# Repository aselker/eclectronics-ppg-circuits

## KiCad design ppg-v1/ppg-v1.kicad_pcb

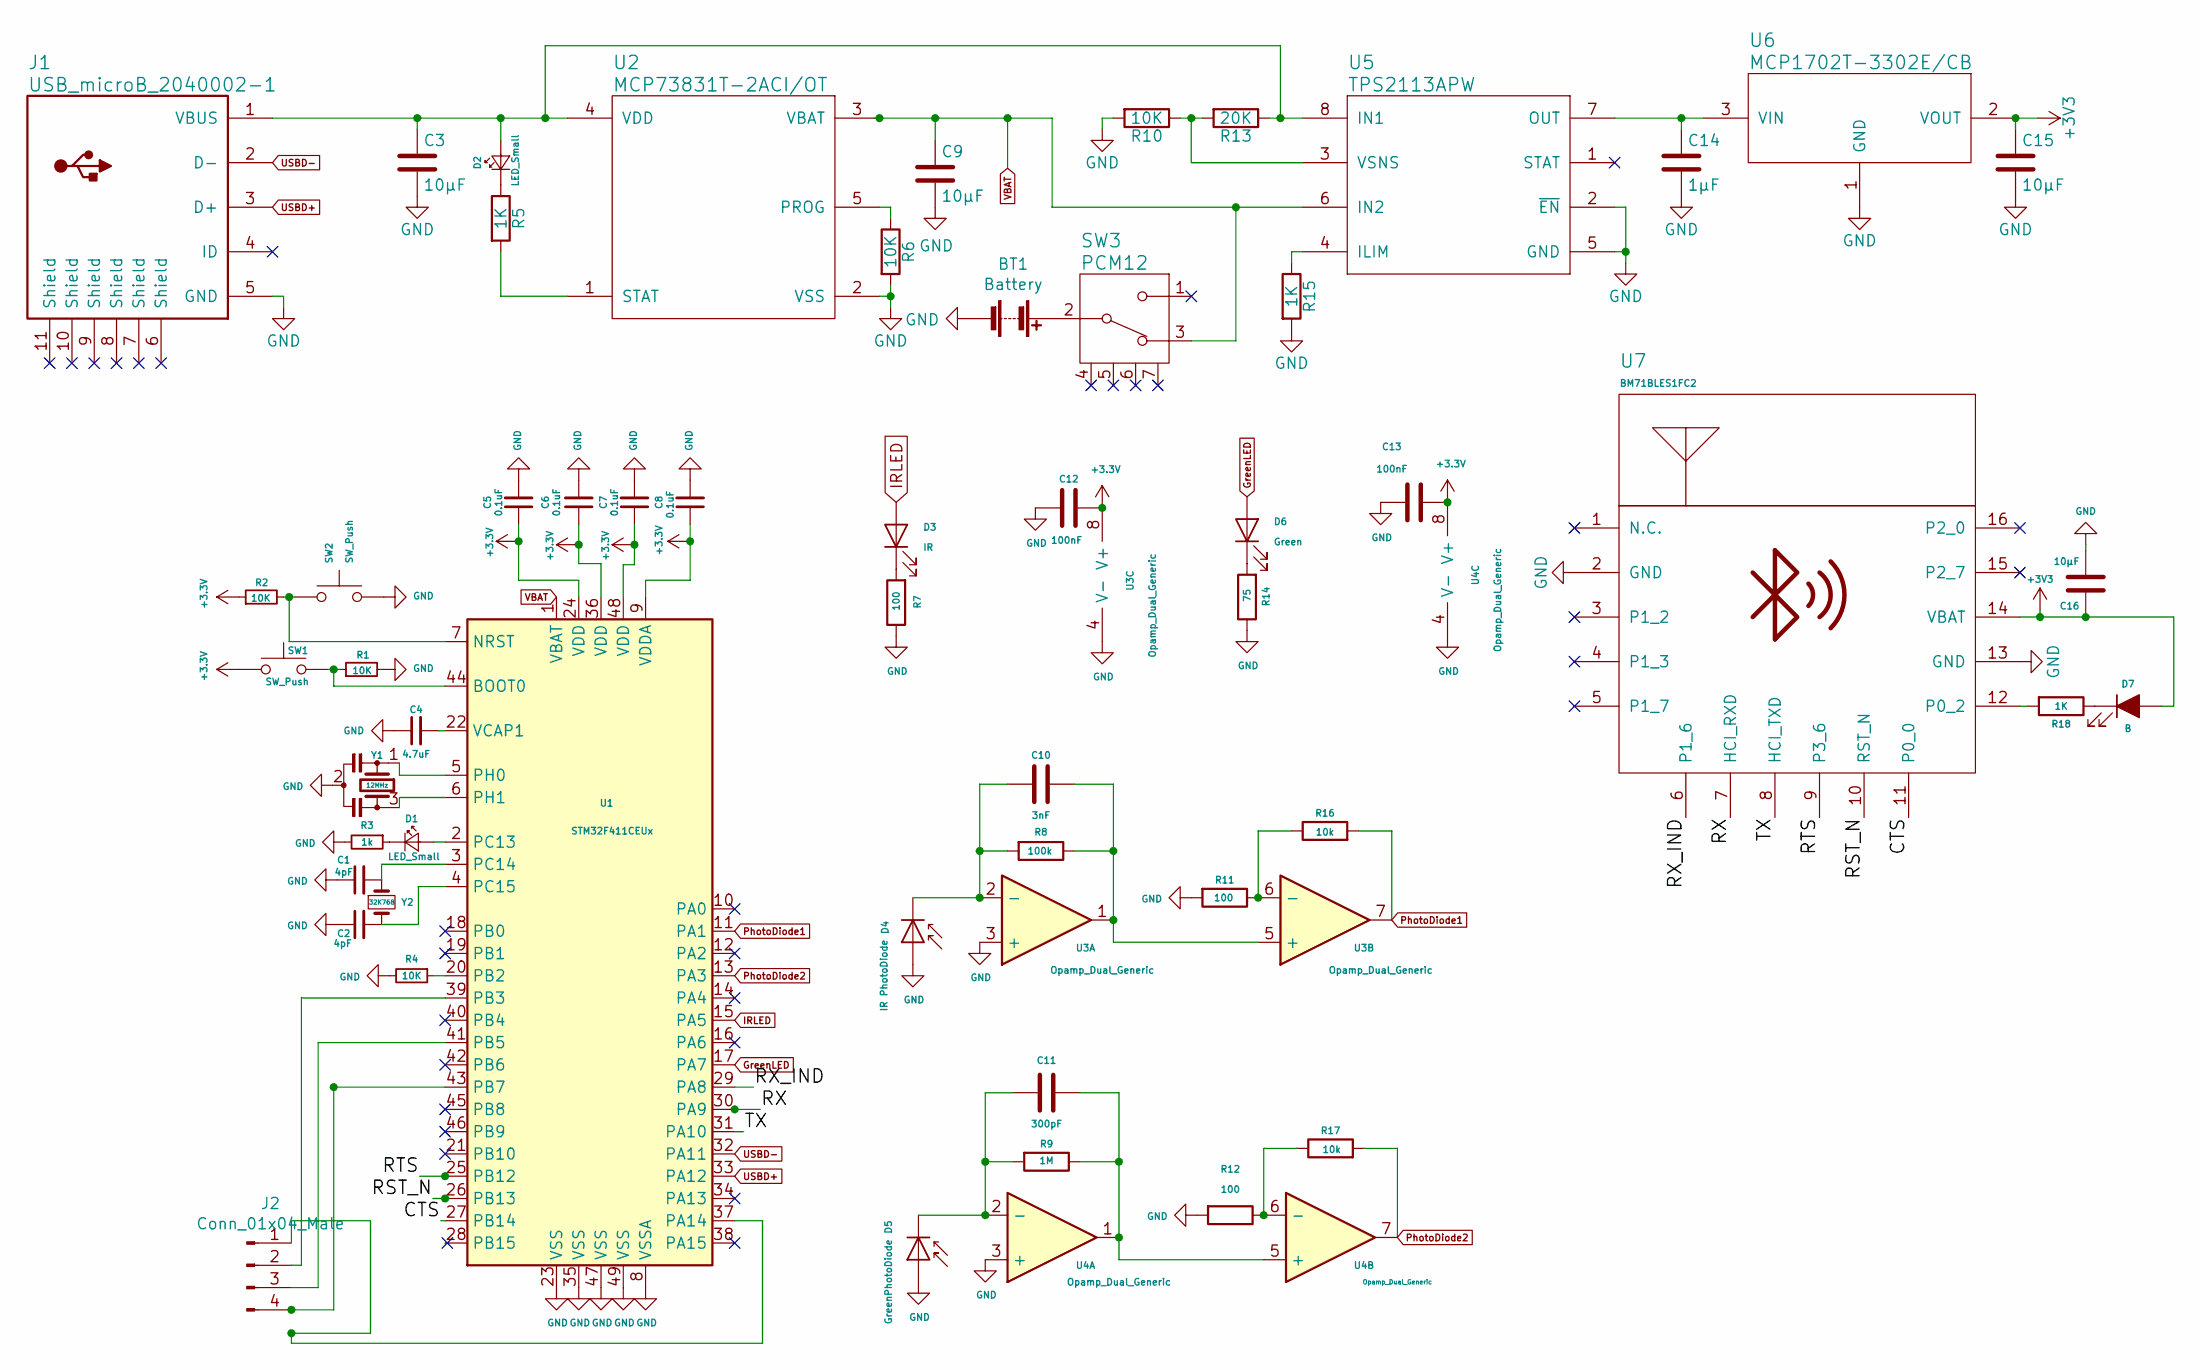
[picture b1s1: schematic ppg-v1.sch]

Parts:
BT1: Battery; PinHeader_1x02_P2.54mm_Vertical
C1, C2: 4pF; C_0603_1608Metric
C3, C9, C15, C16: 10µF; C_0805_2012Metric
C4: 4.7uF; C_0603_1608Metric
C5, C6, C7, C8: 0.1uF; C_0603_1608Metric
C10: 3nF; C_0603_1608Metric
C11: 300pF; C_0603_1608Metric
C12, C13: 100nF; C_0603_1608Metric
C14: 1µF; C_0603_1608Metric
D1, D2: LED_Small; LED_0805_2012Metric
D3: IR; PinHeader_1x02_P2.54mm_Vertical
D4: IR PhotoDiode; PinHeader_1x02_P2.54mm_Vertical
D5: GreenPhotoDiode; PinHeader_1x02_P2.54mm_Vertical
D6: Green; PinHeader_1x02_P2.54mm_Vertical
D7: B; LED_0805_2012Metric
J1: USB_microB_2040002-1
J2: Conn_01x04_Male; PinHeader_1x04_P2.54mm_Vertical
R1, R2, R4, R6, R10: 10K; R_0603_1608Metric
R3: 1k; R_0603_1608Metric
R5, R15, R18: 1K; R_0603_1608Metric
R7, R11, R12: 100; R_0603_1608Metric
R8: 100k; R_0603_1608Metric
R9: 1M; R_0603_1608Metric
R13: 20K; R_0603_1608Metric
R14: 75; R_0603_1608Metric
R16, R17: 10k; R_0603_1608Metric
SW1, SW2: SW_Push; SW_SPST_B3U-1000P
SW3: PCM12
U1: STM32F411CEUx; QFN-48-1EP_7x7mm_P0.5mm_EP5.6x5.6mm
U2: MCP73831T-2ACI/OT; SOT-23-5
U3, U4: Opamp_Dual_Generic; TSSOP-8
U5: TPS2113APW; TSSOP-8
U6: MCP1702T-3302E/CB; SOT-23
U7: BM71BLES1FC2
Y1: 12MHz; CSTNE
Y2: 32K768; ECS-.327-CDX-1082

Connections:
/CTS: U1.27 (PB14), U7.11 (P0_0)
/RST_N: U1.26 (PB13), U7.10 (RST_N)
/RTS: U1.25 (PB12), U7.9 (P3_6)
/RX: U1.30 (PA9), U7.7 (HCI_RXD)
/RX_IND: U1.29 (PA8), U7.6 (P1_6)
/TX: U1.31 (PA10), U7.8 (HCI_TXD)
GND: BT1.2 (-), C1.1, C2.1, C3.2, C4.1, C5.2, C6.2, C7.2, C8.2, C9.2, C12.2, C13.2, C14.2, C15.2, C16.2, D4.2 (A), D5.2 (A), J1.5 (GND), R1.2, R3.2, R4.2, R6.2, R7.1, R10.2, R11.2, R12.2, R14.1, R15.2, SW2.2, U1.8 (VSSA), U1.23 (VSS), U1.35 (VSS), U1.47 (VSS), U1.49 (VSS), U2.2 (VSS), U3.3 (+), U3.4 (V-), U4.3 (+), U4.4 (V-), U5.2 (~EN), U5.5 (GND), U6.1 (GND), U7.2 (GND), U7.13 (GND), Y1.2
GreenLED: D6.2 (A), U1.17 (PA7)
IRLED: D3.2 (A), U1.15 (PA5)
unnamed: BT1.1 (+), SW3.2
unnamed: C1.2, U1.3 (PC14), Y2.1
unnamed: C2.2, U1.4 (PC15), Y2.2
unnamed: C3.1, D2.2 (A), J1.1 (VBUS), R13.1, U2.4 (VDD), U5.8 (IN1)
unnamed: C4.2, U1.22 (VCAP1)
unnamed: C10.1, R8.1, U3.1, U3.5 (+)
unnamed: C10.2, D4.1 (K), R8.2, U3.2 (-)
unnamed: C11.1, R9.1, U4.1, U4.5 (+)
unnamed: C11.2, D5.1 (K), R9.2, U4.2 (-)
unnamed: C14.1, U5.7 (OUT), U6.3 (VIN)
unnamed: D1.1 (K), R3.1
unnamed: D1.2 (A), U1.2 (PC13)
unnamed: D2.1 (K), R5.1
unnamed: D3.1 (K), R7.2
unnamed: D6.1 (K), R14.2
unnamed: D7.1 (K), R18.1
unnamed: J2.1, U1.37 (PA14)
unnamed: J2.2, U1.39 (PB3)
unnamed: J2.3, U1.41 (PB5)
unnamed: J2.4, U1.43 (PB7)
unnamed: R1.1, SW1.2, U1.44 (BOOT0)
unnamed: R2.2, SW2.1, U1.7 (NRST)
unnamed: R4.1, U1.20 (PB2)
unnamed: R5.2, U2.1 (STAT)
unnamed: R6.1, U2.5 (PROG)
unnamed: R10.1, R13.2, U5.3 (VSNS)
unnamed: R11.1, R16.1, U3.6 (-)
unnamed: R12.1, R17.1, U4.6 (-)
unnamed: R15.1, U5.4 (ILIM)
unnamed: R18.2, U7.12 (P0_2)
unnamed: U1.5 (PH0), Y1.1
unnamed: U1.6 (PH1), Y1.3
PhotoDiode1: R16.2, U1.11 (PA1), U3.7
PhotoDiode2: R17.2, U1.13 (PA3), U4.7
USBD+: J1.3 (D+), U1.33 (PA12)
USBD-: J1.2 (D-), U1.32 (PA11)
VBAT: C9.1, SW3.3, U1.1 (VBAT), U2.3 (VBAT), U5.6 (IN2)

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
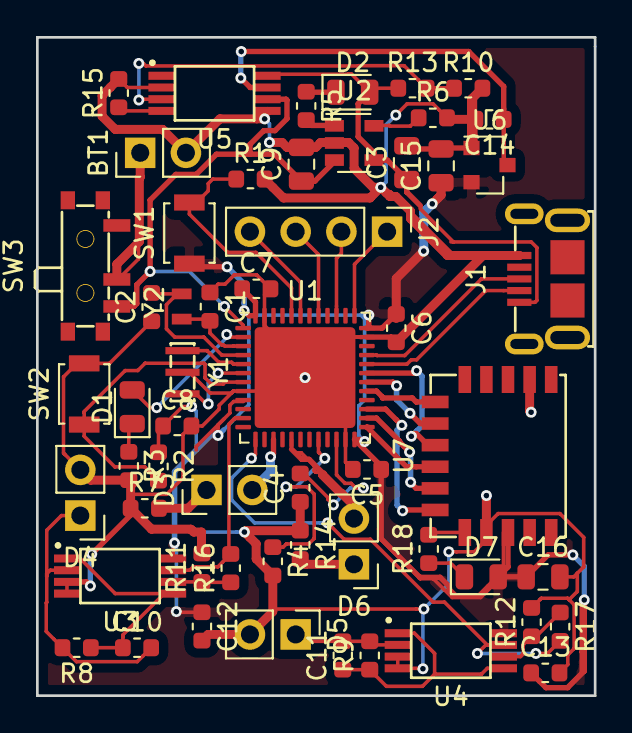
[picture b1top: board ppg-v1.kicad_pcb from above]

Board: 2 copper layers, 31.0 x 36.6 mm, 56 parts (0 on the bottom side), 47 nets.

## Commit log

2019-04-06 initial commit!
2019-04-06 circuits
2019-04-08 More schematic
2019-04-08 s/ 50 / 30 /g; to replace text sizes
2019-04-08 add tmp file with parts from paper plane controller
2019-04-08 import parts from paper plane
2019-04-11 add led/photodiode subsystem
2019-04-11 Added the LED/photodiode circuits.
2019-04-11 Added everything together, moved things around, added a battery, and made some changes to the circuitry controlling charging etc
2019-04-11 Fixed some offset parts and a disconnect between a part and GND
2019-04-15 updated bak
2019-04-15 new one
2019-04-15 adding everything
2019-04-16 Replace led footprint, move switch, route things
2019-04-16 Rebuilding pcb layout
2019-04-16 Draft 1 of the PCBgit add .
2019-04-17 fix buttons
2019-04-17 fix edge cuts
2019-04-17 more traces and edge cuts
2019-04-17 fix fills
2019-04-17 small fixes
2019-04-24 replace op-amp footprints soic -> tssop
2019-04-24 finish arranging new footprints
2019-04-25 new footprint for resonator
2019-04-25 stuff...
2019-04-25 footprints
2019-05-02 Connect hardware serial pins on stm32 to Bluetooth module
